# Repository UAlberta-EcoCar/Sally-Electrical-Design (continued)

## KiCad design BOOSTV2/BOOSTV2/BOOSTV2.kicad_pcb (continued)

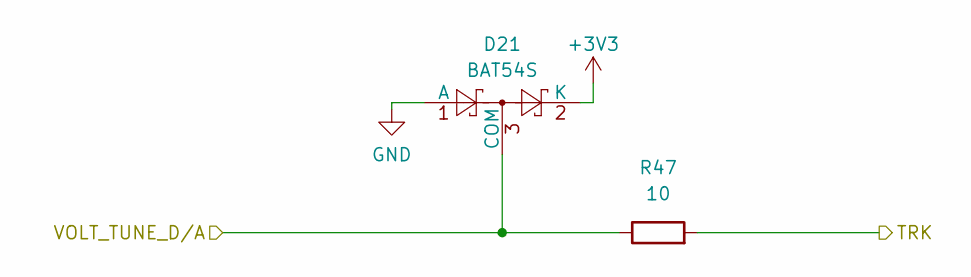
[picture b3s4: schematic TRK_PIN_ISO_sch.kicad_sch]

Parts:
D21: BAT54S; SOT-23
R47: 10; R_0603_1608Metric

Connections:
+3V3: D21.2 (K); also elsewhere on the board
/Boost-Circuit/TRK: R47.2; also elsewhere on the board
/Low Side/VOLT_TUNE_D/A: D21.3 (COM), R47.1; also elsewhere on the board
GND: D21.1 (A); also elsewhere on the board

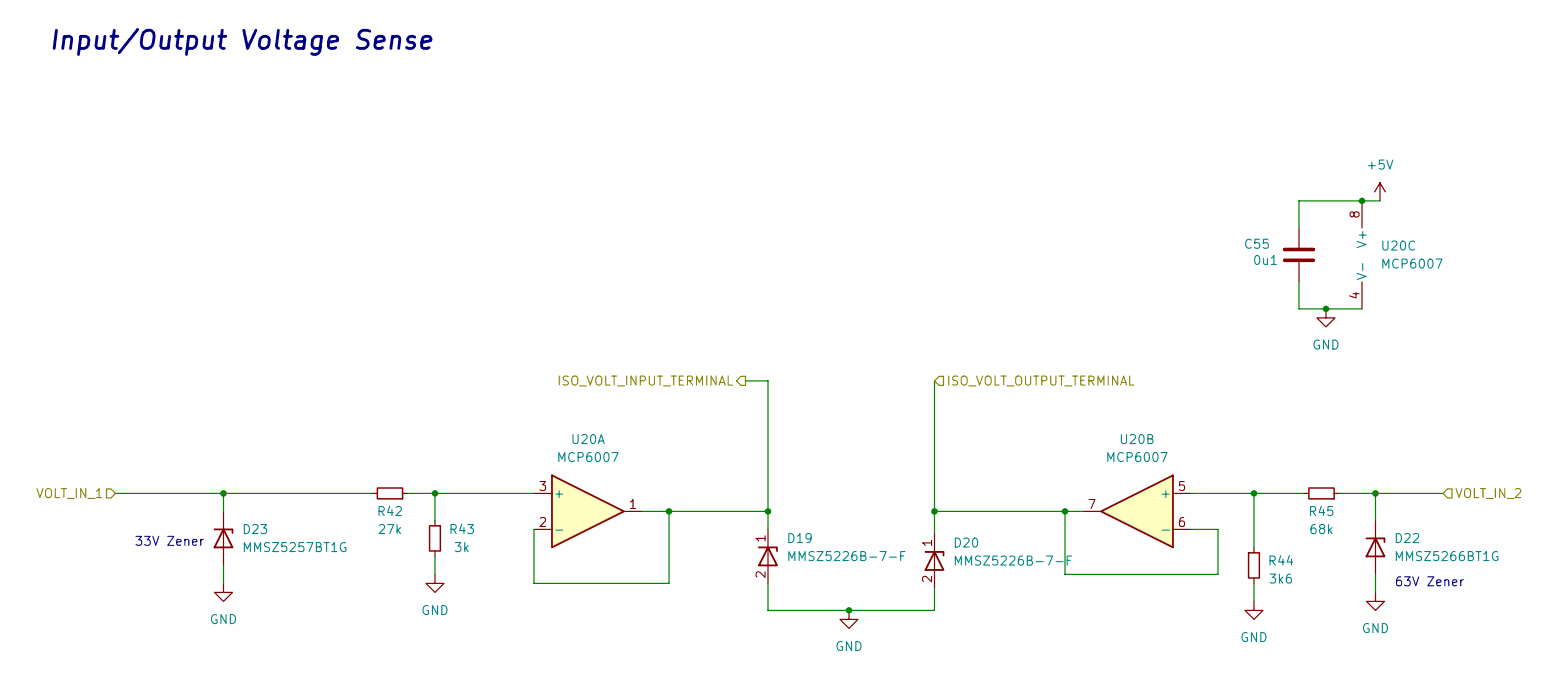
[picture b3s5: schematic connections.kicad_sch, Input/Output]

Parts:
C55: 0u1; C_0603_1608Metric
D19, D20: MMSZ5226B-7-F; D_SOD_123_M; Part# C155250
D22: MMSZ5266BT1G; D_SOD-123
D23: MMSZ5257BT1G; D_SOD-123
R42: 27k; R_0603_1608Metric
R43: 3k; R_0603_1608Metric; Part# C25811
R44: 3k6; R_0603_1608Metric
R45: 68k; R_0603_1608Metric
U20: MCP6007; SOIC-8_3.9x4.9mm_P1.27mm

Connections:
+5V: C55.1, U20.8 (V+); also elsewhere on the board
/Boost-Circuit/VOLT_IN_1: D23.1 (K), R42.2; also elsewhere on the board
/Boost-Circuit/VOLT_IN_2: D22.1 (K), R45.1; also elsewhere on the board
/Low Side/ISO_VOLT_INPUT_TERMINAL: D19.1, U20.1, U20.2 (-); also elsewhere on the board
/Low Side/ISO_VOLT_OUTPUT_TERMINAL: D20.1, U20.6 (-), U20.7; also elsewhere on the board
GND: C55.2, D19.2, D20.2, D22.2 (A), D23.2 (A), R43.2, R44.2, U20.4 (V-); also elsewhere on the board
unnamed: R42.1, R43.1, U20.3 (+)
unnamed: R44.1, R45.2, U20.5 (+)

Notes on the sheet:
33V Zener
Input/Output Voltage Sense
63V Zener

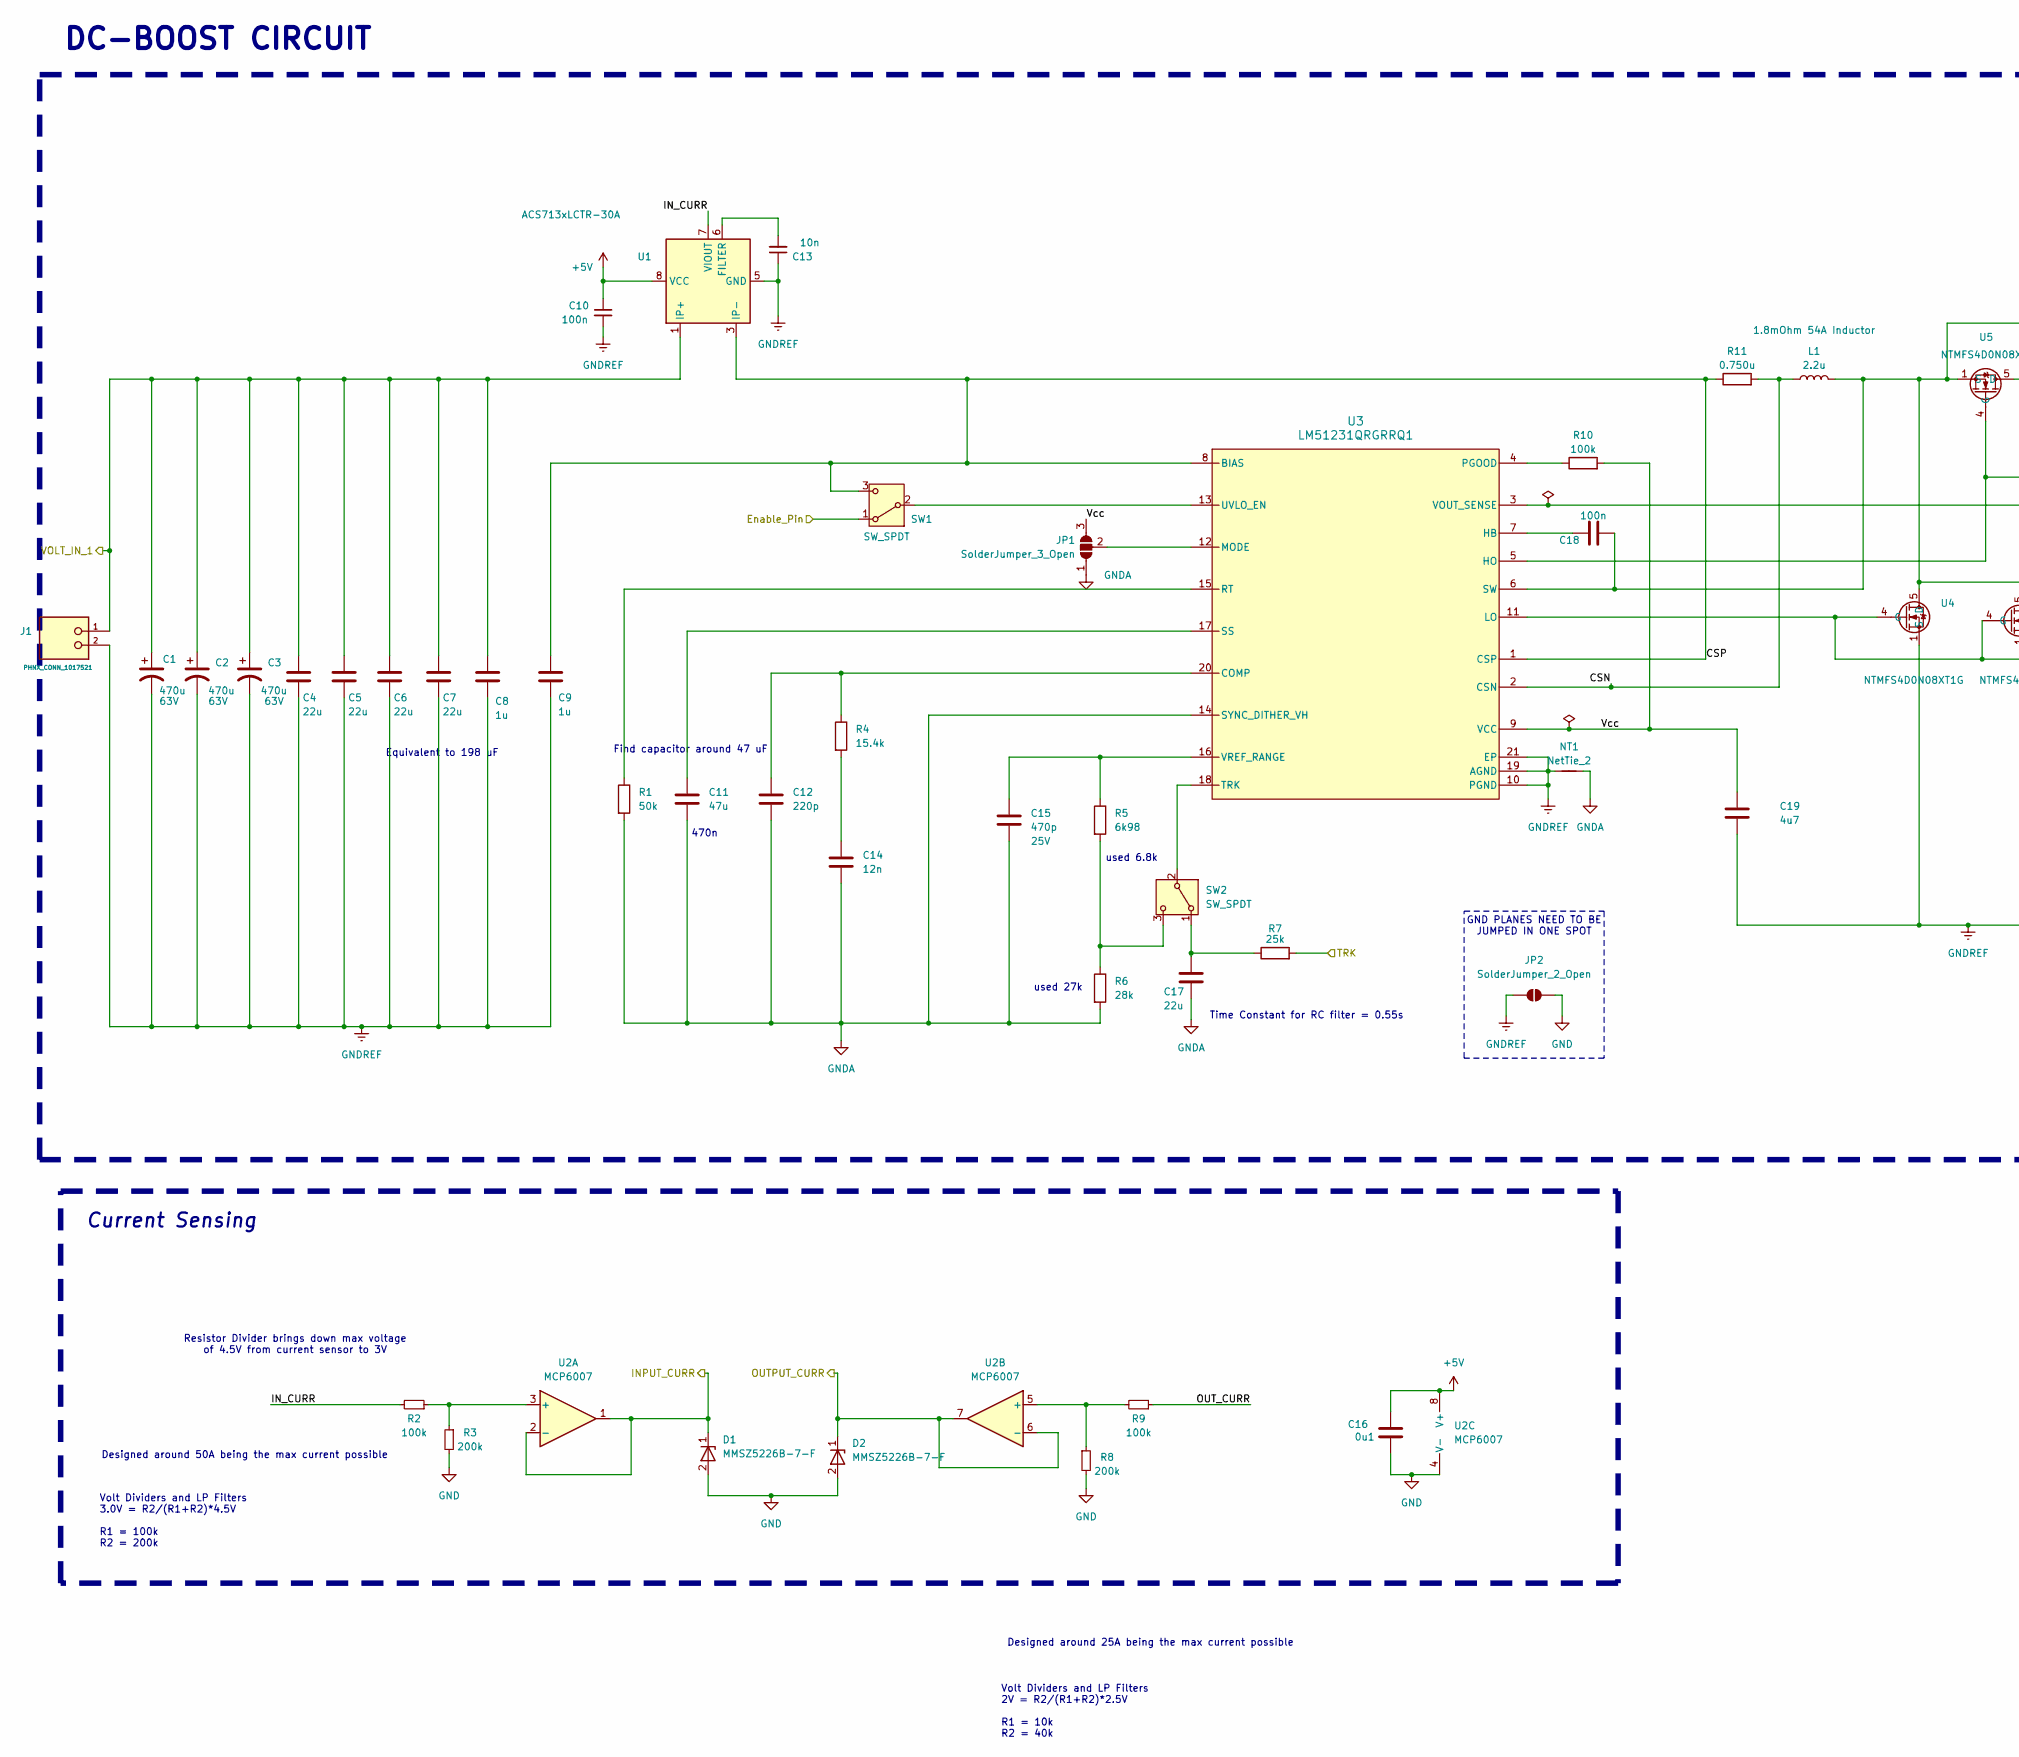
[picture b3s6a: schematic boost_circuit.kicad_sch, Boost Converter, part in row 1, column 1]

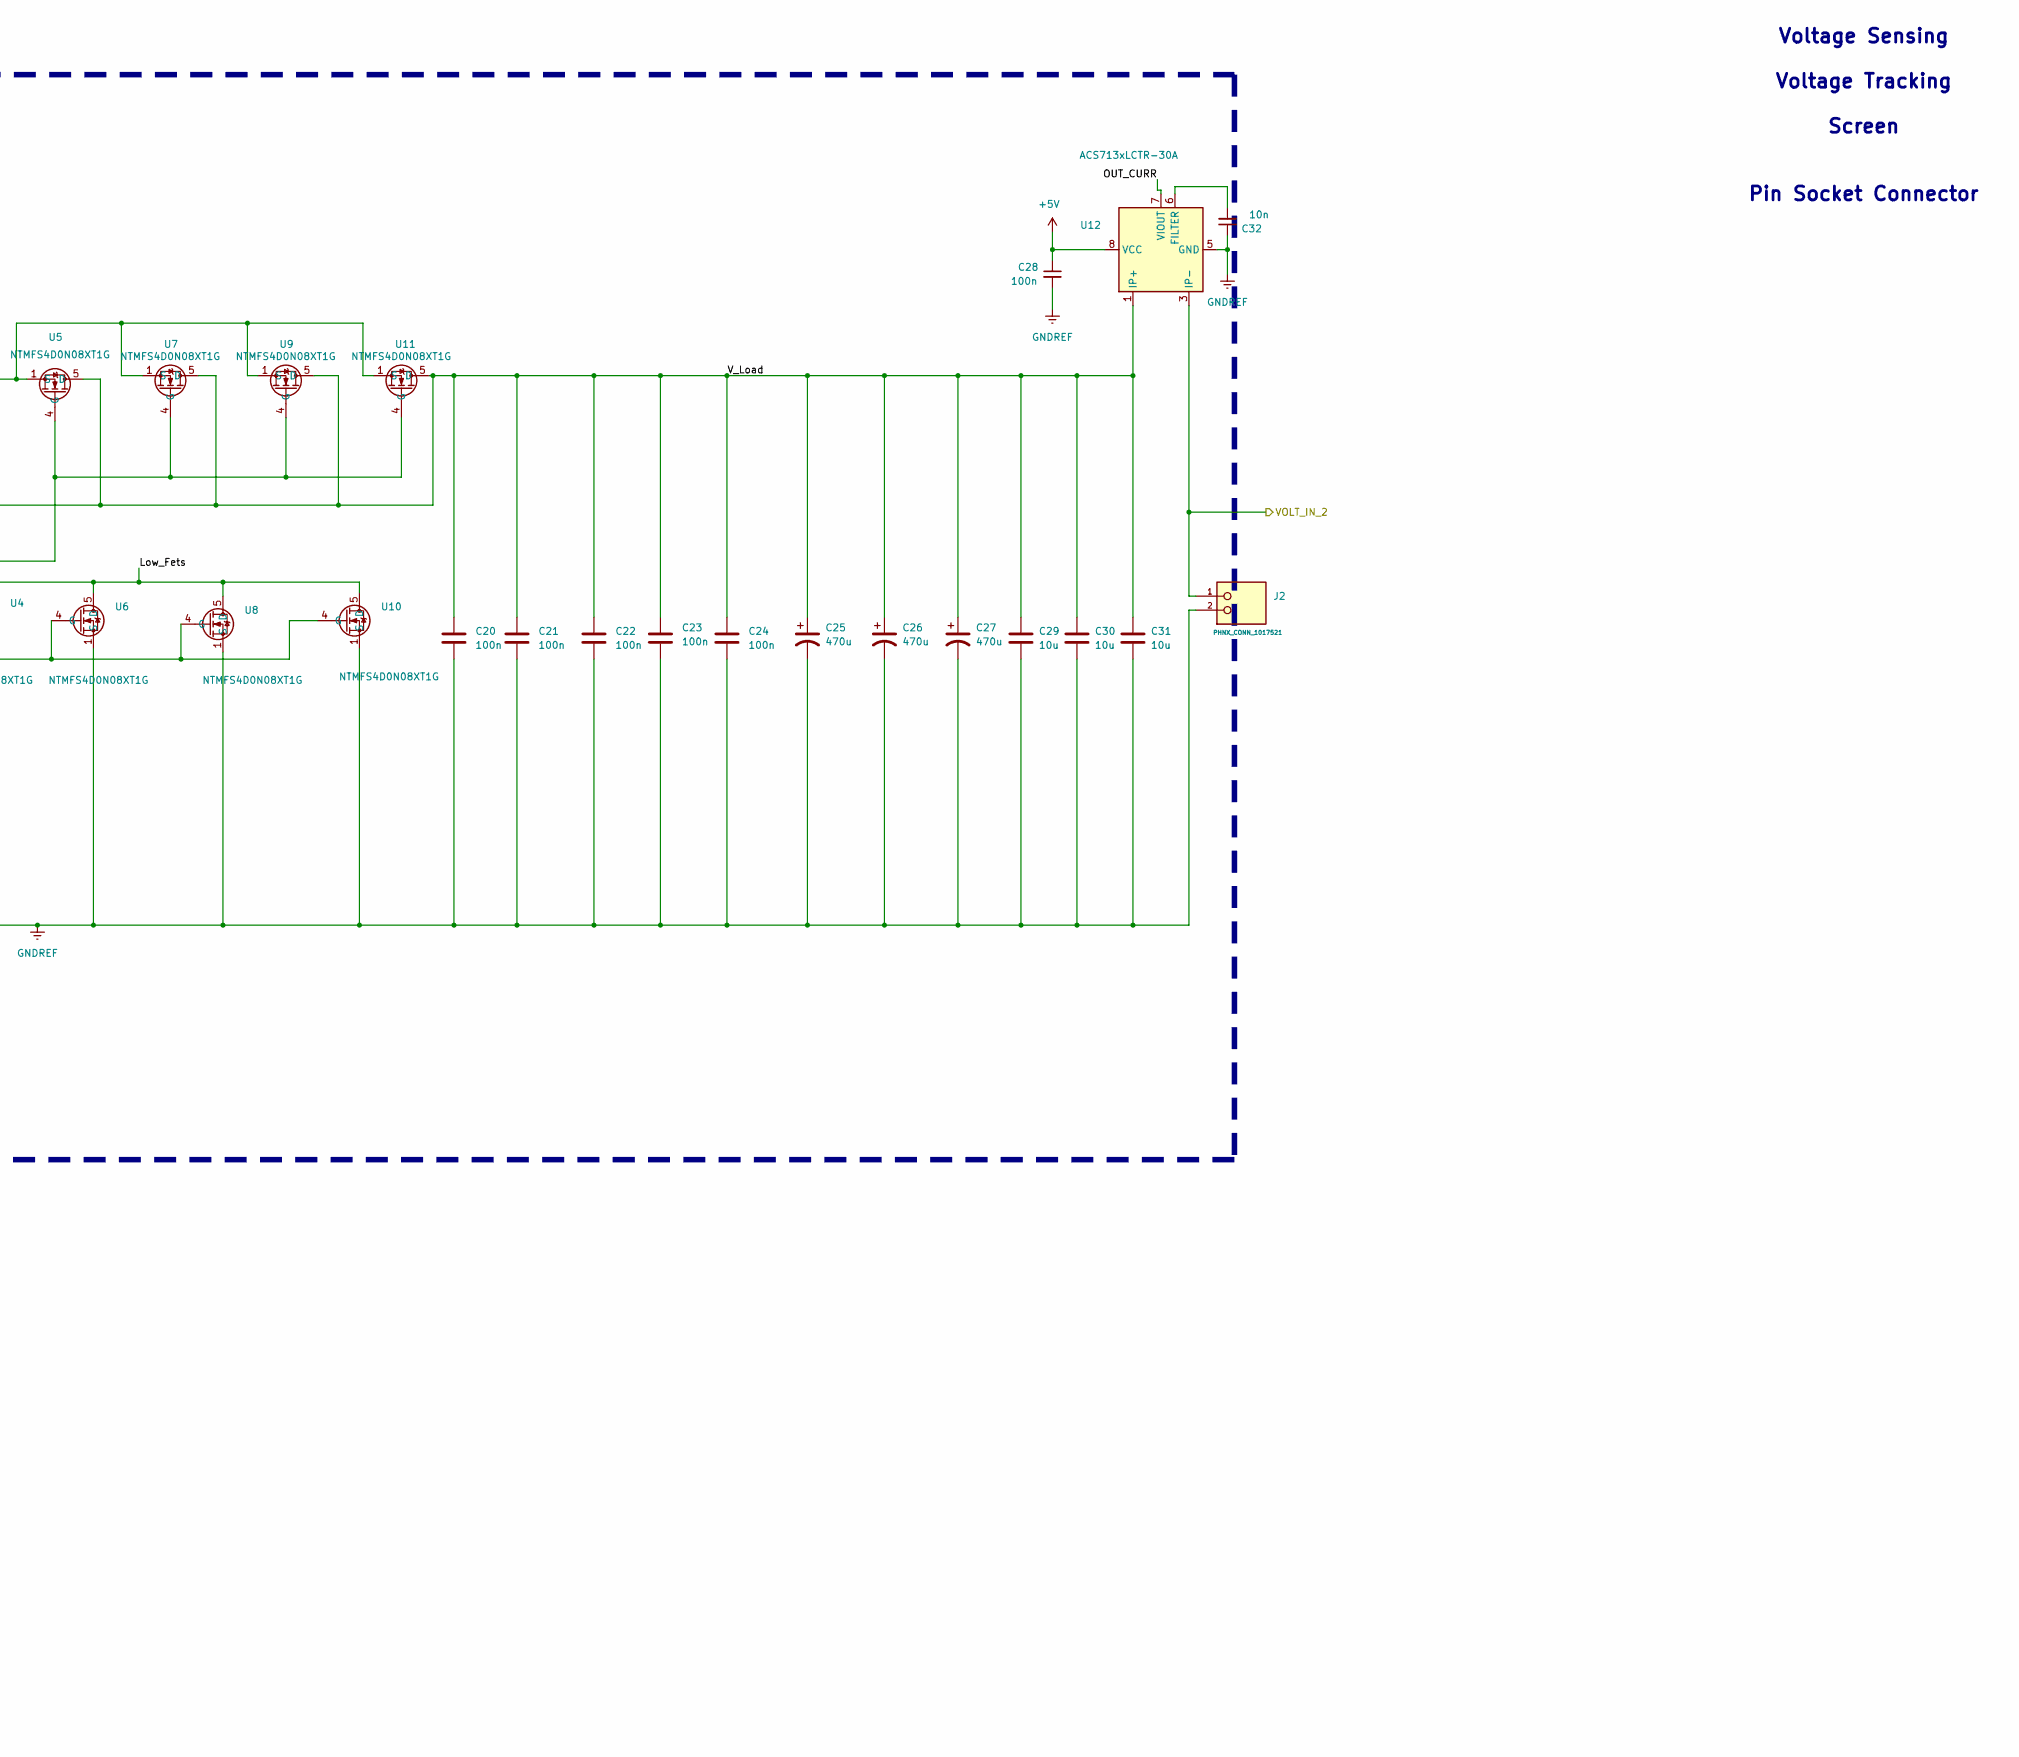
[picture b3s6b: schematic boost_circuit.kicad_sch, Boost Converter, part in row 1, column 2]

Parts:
C1, C2, C3: 470u; CAP_PAN_10X20_PAN; Part # ECA-1HM471B
C4, C5, C6, C7: 22u; C_0805_2012Metric
C8, C9: 1u; C_0603_1608Metric
C10, C28: 100n; C_0603_1608Metric; Part# C88219
C11: 47u; C_0603_1608Metric
C12: 220p; C_0805_2012Metric
C13, C32: 10n; C_0603_1608Metric; Part# C88219
C14: 12n; C_0603_1608Metric
C15: 470p; C_0603_1608Metric; Rating 25V
C16: 0u1; C_0603_1608Metric
C17: 22u; C_0603_1608Metric
C18: 100n; R_0603_1608Metric
C19: 4u7; C_0603_1608Metric
C20, C21, C22, C23, C24: 100n; C_0603_1608Metric
C25, C26, C27: 470u; CAP_YX_16X31P5_RUB; Part # 100ZLH470MEFC16X31.5
C29, C30, C31: 10u; C_1210_3225Metric
D1, D2: MMSZ5226B-7-F; D_SOD_123_M; Part# C155250
J1, J2: PHNX_CONN_1017521; PHOENIX_1017521; PARTREV 04.01.2018
JP1: SolderJumper_3_Open; SolderJumper-3_P1.3mm_Open_RoundedPad1.0x1.5mm_NumberLabels
JP2: SolderJumper_2_Open; SolderJumper-2_P1.3mm_Open_RoundedPad1.0x1.5mm
L1: 2.2u; L_Kemet_3u3
NT1: NetTie_2; NetTie-2_SMD_Pad0.5mm
R1: 50k; R_0603_1608Metric
R2, R9, R10: 100k; R_0603_1608Metric
R3: 200k; R_0603_1608Metric; Part# C25811
R4: 15.4k; R_0603_1608Metric_Pad0.98x0.95mm_HandSolder
R5: 6k98; R_0603_1608Metric
R6: 28k; R_0603_1608Metric
R7: 25k; R_0603_1608Metric
R8: 200k; R_0603_1608Metric
R11: 0.750u; CSS2H3920RL700F
SW1, SW2: SW_SPDT; PinHeader_1x03_P2.54mm_Vertical
U1, U12: ACS713xLCTR-30A; SOIC-8_3.9x4.9mm_P1.27mm
U2: MCP6007; SOIC-8_3.9x4.9mm_P1.27mm
U3: LM51231QRGRRQ1; RGR0020C-MFG
U4, U5, U6, U7, U8, U9, U10, U11: NTMFS4D0N08XT1G; PowerMosDFNHybrid

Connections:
+5V: C10.1, C16.1, C28.1, U1.8 (VCC), U2.8 (V+), U12.8 (VCC); also elsewhere on the board
/Boost-Circuit/CSN: L1.1, R11.2, U3.2 (CSN)
/Boost-Circuit/CSP: C9.1, R11.1, SW1.3 (C), U1.3 (IP-), U1.4 (IP-), U3.1 (CSP), U3.8 (BIAS)
/Boost-Circuit/Enable_Pin: SW1.1 (A); also elsewhere on the board
/Boost-Circuit/INPUT_CURR: D1.1, U2.1, U2.2 (-); also elsewhere on the board
/Boost-Circuit/IN_CURR: R2.2, U1.7 (VIOUT)
/Boost-Circuit/Low_Fets: C18.1, L1.2, U3.6 (SW), U4.5 (D), U5.1 (S), U5.2 (S), U5.3 (S), U6.5 (D), U7.1 (S), U7.2 (S), U7.3 (S), U8.5 (D), U9.1 (S), U9.2 (S), U9.3 (S), U10.5 (D), U11.1 (S), U11.2 (S), U11.3 (S)
/Boost-Circuit/OUTPUT_CURR: D2.1, U2.6 (-), U2.7; also elsewhere on the board
/Boost-Circuit/OUT_CURR: R9.1, U12.7 (VIOUT)
/Boost-Circuit/TRK: R7.2; also elsewhere on the board
/Boost-Circuit/VOLT_IN_1: C1.1, C2.1, C3.1, C4.1, C5.1, C6.1, C7.1, C8.1, J1.1, U1.1 (IP+), U1.2 (IP+); also elsewhere on the board
/Boost-Circuit/VOLT_IN_2: J2.1, U12.3 (IP-), U12.4 (IP-); also elsewhere on the board
/Boost-Circuit/V_Load: C20.1, C21.1, C22.1, C23.1, C24.1, C25.1, C26.1, C27.1, C29.1, C30.1, C31.1, U3.3 (VOUT_SENSE), U5.5 (D), U7.5 (D), U9.5 (D), U11.5 (D), U12.1 (IP+), U12.2 (IP+)
/Boost-Circuit/Vcc: C19.1, JP1.3 (B), R10.2, U3.9 (VCC)
GND: C16.2, D1.2, D2.2, JP2.2 (B), R3.2, R8.2, U2.4 (V-); also elsewhere on the board
GNDA: C11.2, C12.2, C14.2, C15.2, C17.2, JP1.1 (A), NT1.2, R1.2, R6.2, U3.14 (SYNC_DITHER_VH)
GNDREF: C1.2, C2.2, C3.2, C4.2, C5.2, C6.2, C7.2, C8.2, C9.2, C10.2, C13.1, C19.2, C20.2, C21.2, C22.2, C23.2, C24.2, C25.2, C26.2, C27.2, C28.2, C29.2, C30.2, C31.2, C32.1, J1.2, J2.2, JP2.1 (A), NT1.1, U1.5 (GND), U3.10 (PGND), U3.19 (AGND), U3.21 (EP), U4.1 (S), U4.2 (S), U4.3 (S), U6.1 (S), U6.2 (S), U6.3 (S), U8.1 (S), U8.2 (S), U8.3 (S), U10.1 (S), U10.2 (S), U10.3 (S), U12.5 (GND)
unnamed: C14.1, R4.2
unnamed: JP1.2 (C), U3.12 (MODE)
unnamed: SW1.2 (B), U3.13 (UVLO_EN)
unnamed: C17.1, R7.1, SW2.1 (A)
unnamed: SW2.2 (B), U3.18 (TRK)
unnamed: R5.2, R6.1, SW2.3 (C)
unnamed: C13.2, U1.6 (FILTER)
unnamed: R2.1, R3.1, U2.3 (+)
unnamed: R8.1, R9.2, U2.5 (+)
unnamed: C12.1, R4.1, U3.20 (COMP)
unnamed: C18.2, U3.7 (HB)
unnamed: R10.1, U3.4 (PGOOD)
unnamed: R1.1, U3.15 (RT)
unnamed: C11.1, U3.17 (SS)
unnamed: C15.1, R5.1, U3.16 (VREF_RANGE)
unnamed: U3.11 (LO), U4.4 (G), U6.4 (G), U8.4 (G), U10.4 (G)
unnamed: U3.5 (HO), U5.4 (G), U7.4 (G), U9.4 (G), U11.4 (G)
unnamed: C32.2, U12.6 (FILTER)

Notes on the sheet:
used 27k
DC-BOOST CIRCUIT
Resistor Divider brings down max voltage of 4.5V from current sensor to 3V
470n
used 6.8k
Volt Dividers and LP Filters 3.0V = R2/(R1+R2)*4.5V R1 = 100k R2 = 200k
Time Constant for RC filter = 0.55s
Volt Dividers and LP Filters 2V = R2/(R1+R2)*2.5V R1 = 10k R2 = 40k
Current Sensing
GND PLANES NEED TO BE JUMPED IN ONE SPOT
Voltage Sensing Voltage Tracking Screen Pin Socket Connector
Designed around 25A being the max current possible
Find capacitor around 47 uF
Designed around 50A being the max current possible
Equivalent to 198 uF

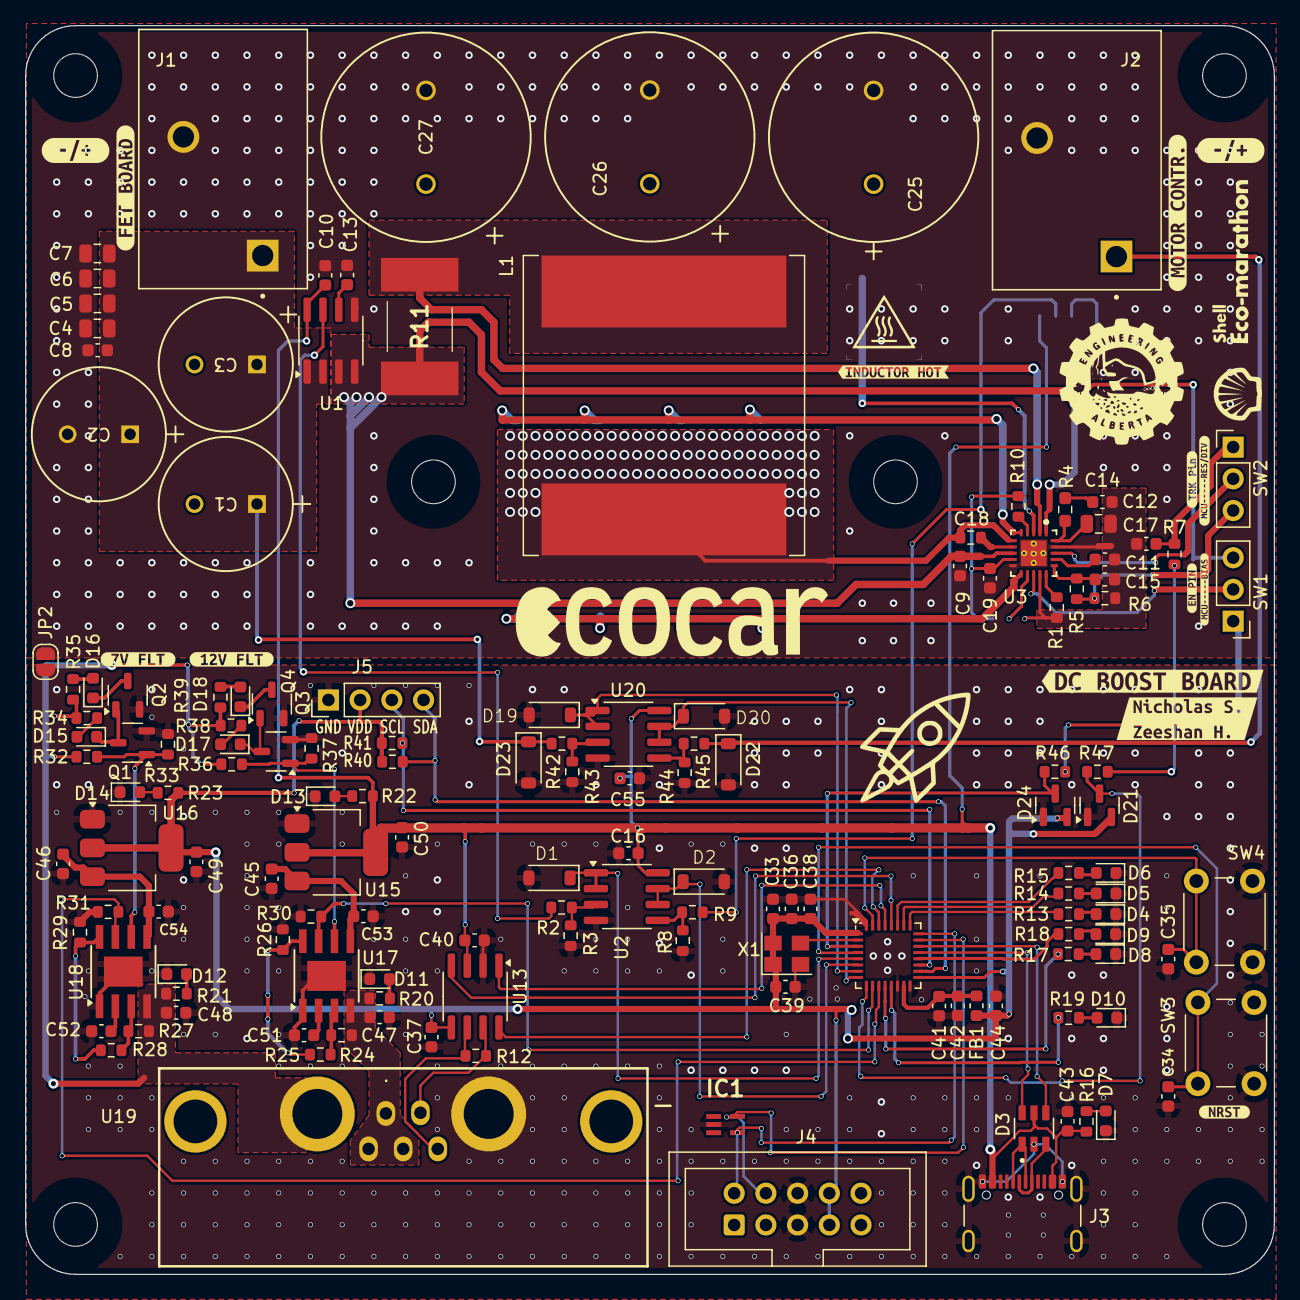
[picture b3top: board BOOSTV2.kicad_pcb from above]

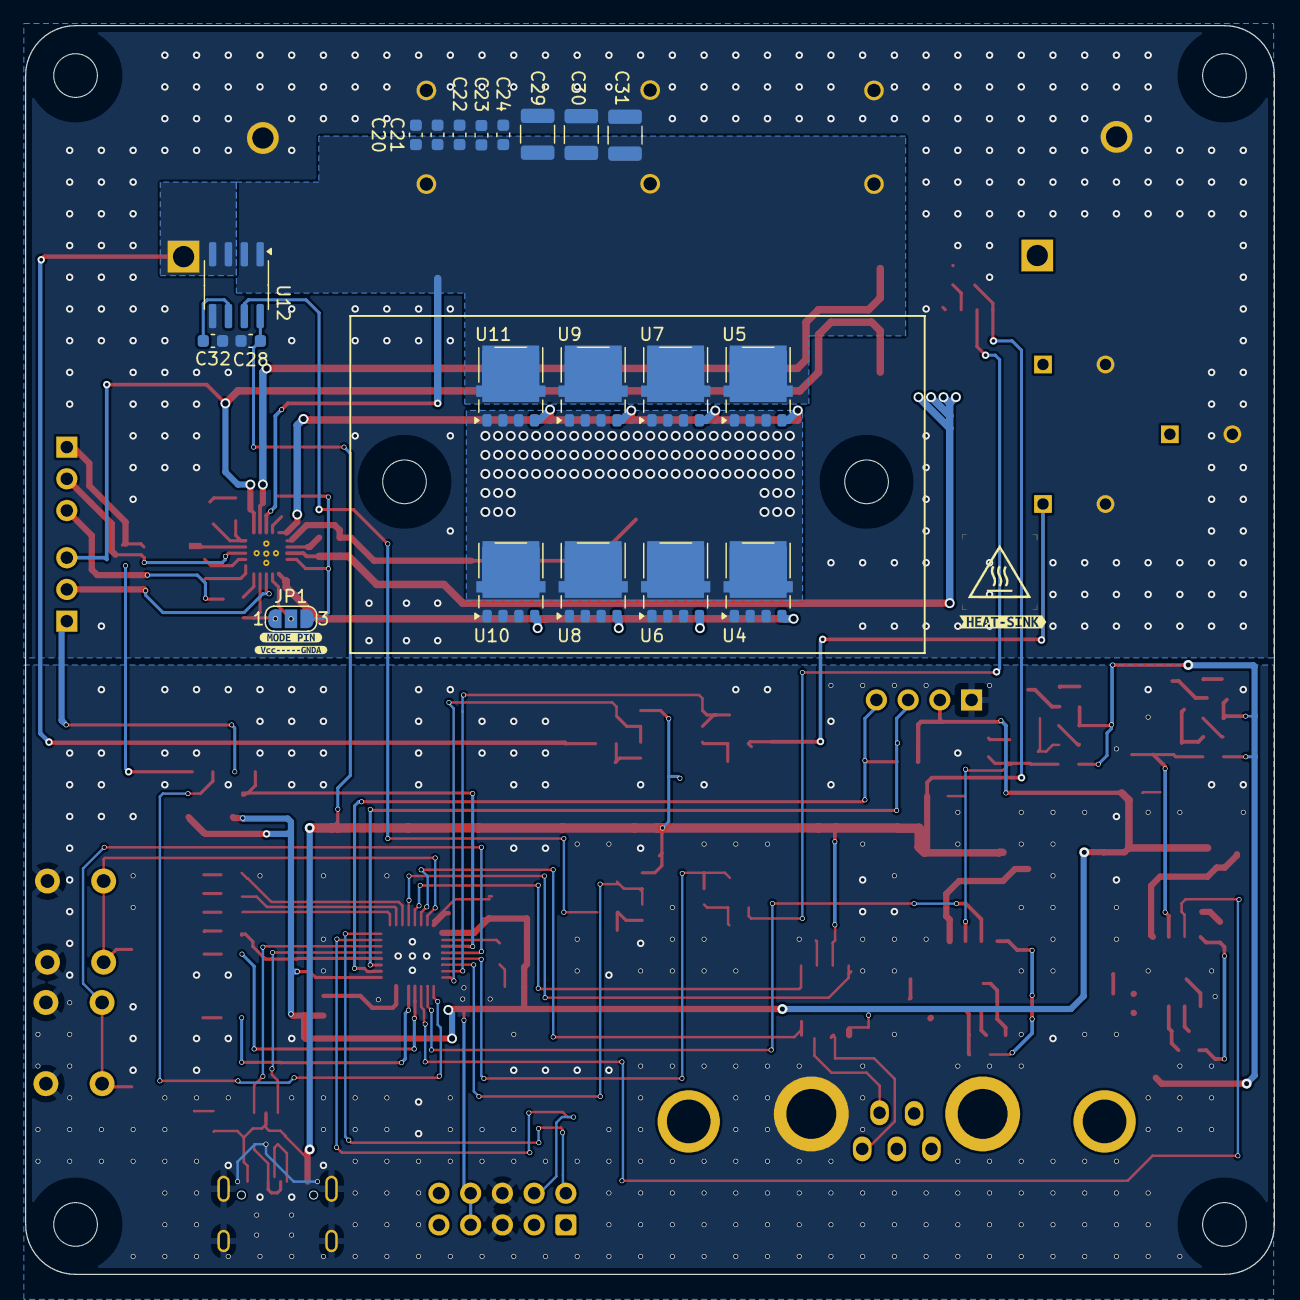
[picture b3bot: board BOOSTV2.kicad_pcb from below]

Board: 2 copper layers, 100.0 x 100.0 mm, 189 parts (23 on the bottom side), 98 nets.

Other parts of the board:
kibuzzard-67B8F6AB: G***; kibuzzard-67B8F6AB
kibuzzard-67B8F68E: G***; kibuzzard-67B8F68E
kibuzzard-67B8F697: G***; kibuzzard-67B8F697
kibuzzard-67B37C45: G***; kibuzzard-67B37C45
kibuzzard-67B37DE2: G***; kibuzzard-67B37DE2
kibuzzard-67B58E6E: G***; kibuzzard-67B58E6E
kibuzzard-67B58E58: G***; kibuzzard-67B58E58
kibuzzard-67B540FD: G***; kibuzzard-67B540FD
kibuzzard-67B591A9: G***; kibuzzard-67B591A9
kibuzzard-67B59132: G***; kibuzzard-67B59132
kibuzzard-67BA3C10: G***; kibuzzard-67BA3C10
kibuzzard-67BA360B: G***; kibuzzard-67BA360B
kibuzzard-67BA362A: G***; kibuzzard-67BA362A
kibuzzard-6743FE6D: G***; kibuzzard-6743FE6D
kibuzzard-6743FE8B: G***; kibuzzard-6743FE8B
kibuzzard-67392652, kibuzzard-67392652#2: G***; kibuzzard-67392652

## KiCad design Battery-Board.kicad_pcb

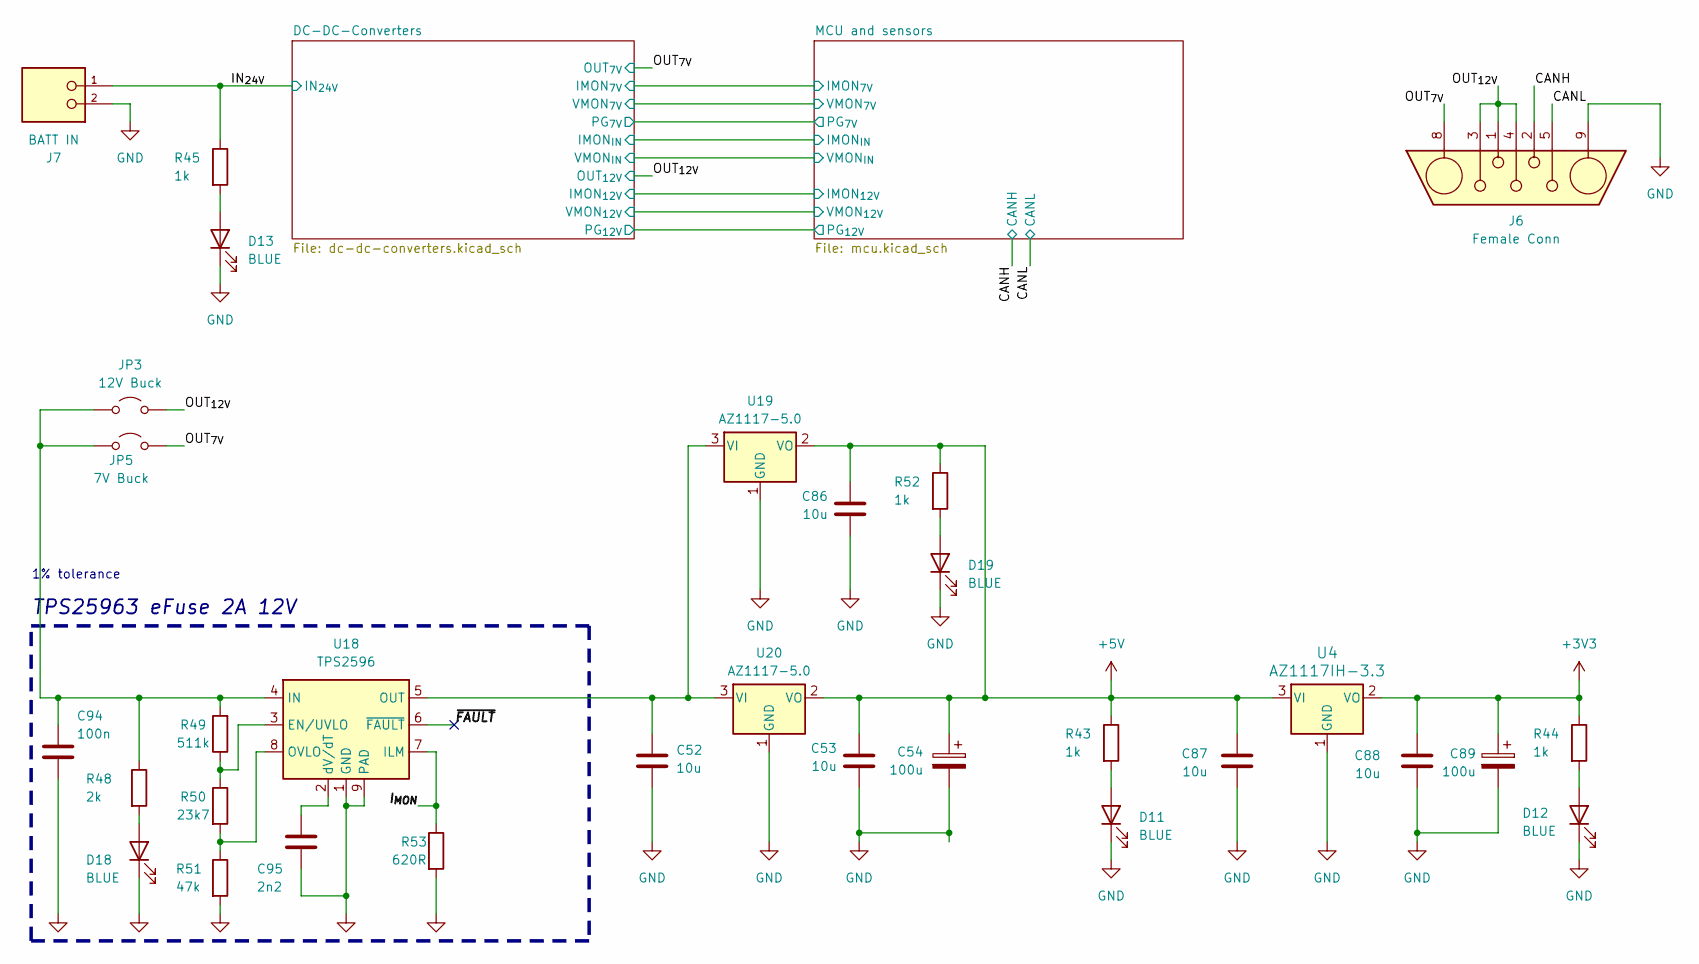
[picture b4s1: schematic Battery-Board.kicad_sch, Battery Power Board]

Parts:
C52, C53, C86, C87, C88: 10u; C_0805_2012Metric; LCSC# C15850
C54, C89: 100u; CP_Elec_6.3x9.9; LCSC# C72478
C94: 100n; C_0603_1608Metric; JLCPCB Part#(Optional) C28233
C95: 2n2; C_0603_1608Metric; JLCPCB Part#(Optional) C1531
D11, D12, D13, D18, D19: BLUE; LED_0603_1608Metric
J6: Female Conn; DB7W2-Female
J7: BATT IN; PHOENIX_1017521; PARTREV 04.01.2018
JP3: 12V Buck; J_0603_Triangular
JP5: 7V Buck; J_0603_Triangular
R43, R44, R45, R52: 1k; R_0603_1608Metric
R48: 2k; R_0603_1608Metric; JLCPCB Part#(Optional) C17604
R49: 511k; R_0603_1608Metric; JLCPCB Part#(optional) C17709
R50: 23k7; R_0603_1608Metric; JLCPCB Part#(optional) C17480
R51: 47k; R_0603_1608Metric; JLCPCB Part#(optional) C17713
R53: 620R; R_0603_1608Metric; JLCPCB Part#(Optional) C23220
U4: AZ1117IH-3.3; SOT-223-3_TabPin2
U18: TPS2596; TI_SO-PowerPAD-8
U19, U20: AZ1117-5.0; SOT-223-3_TabPin2

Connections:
+3V3: C88.1, C89.1, R44.1, U4.2 (VO); also elsewhere on the board
+5V: C53.1, C54.1, C86.1, C87.1, R43.1, R52.1, U4.3 (VI), U19.2 (VO), U20.2 (VO); also elsewhere on the board
/CANH: J6.2; also elsewhere on the board
/CANL: J6.5; also elsewhere on the board
/IN_{24V}: J7.1, R45.1; also elsewhere on the board
/I_{MON}: R53.1, U18.7 (ILM)
/OUT_{7V}: J6.8, JP5.2 (B); also elsewhere on the board
/OUT_{12V}: J6.1, J6.3, J6.4, JP3.2 (B); also elsewhere on the board
/~FAULT: U18.6 (~FAULT)
GND: C52.2, C53.2, C54.2, C86.2, C87.2, C88.2, C89.2, C94.2, C95.2, D11.1 (K), D12.1 (K), D13.1 (K), D18.1 (K), D19.1 (K), J6.9, J7.2, R51.2, R53.2, U4.1 (GND), U18.1 (GND), U18.9 (PAD), U19.1 (GND), U20.1 (GND); also elsewhere on the board
unnamed: D11.2 (A), R43.2
unnamed: D12.2 (A), R44.2
unnamed: D13.2 (A), R45.2
unnamed: D18.2 (A), R48.2
unnamed: D19.2 (A), R52.2
unnamed: C94.1, JP3.1 (A), JP5.1 (A), R48.1, R49.2, U18.4 (IN)
unnamed: R49.1, R50.1, U18.3 (EN/UVLO)
unnamed: C52.1, U18.5 (OUT), U19.3 (VI), U20.3 (VI)
unnamed: R50.2, R51.1, U18.8 (OVLO)
unnamed: C95.1, U18.2 (dV/dT)

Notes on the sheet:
TPS25963 eFuse 2A 12V
1% tolerance

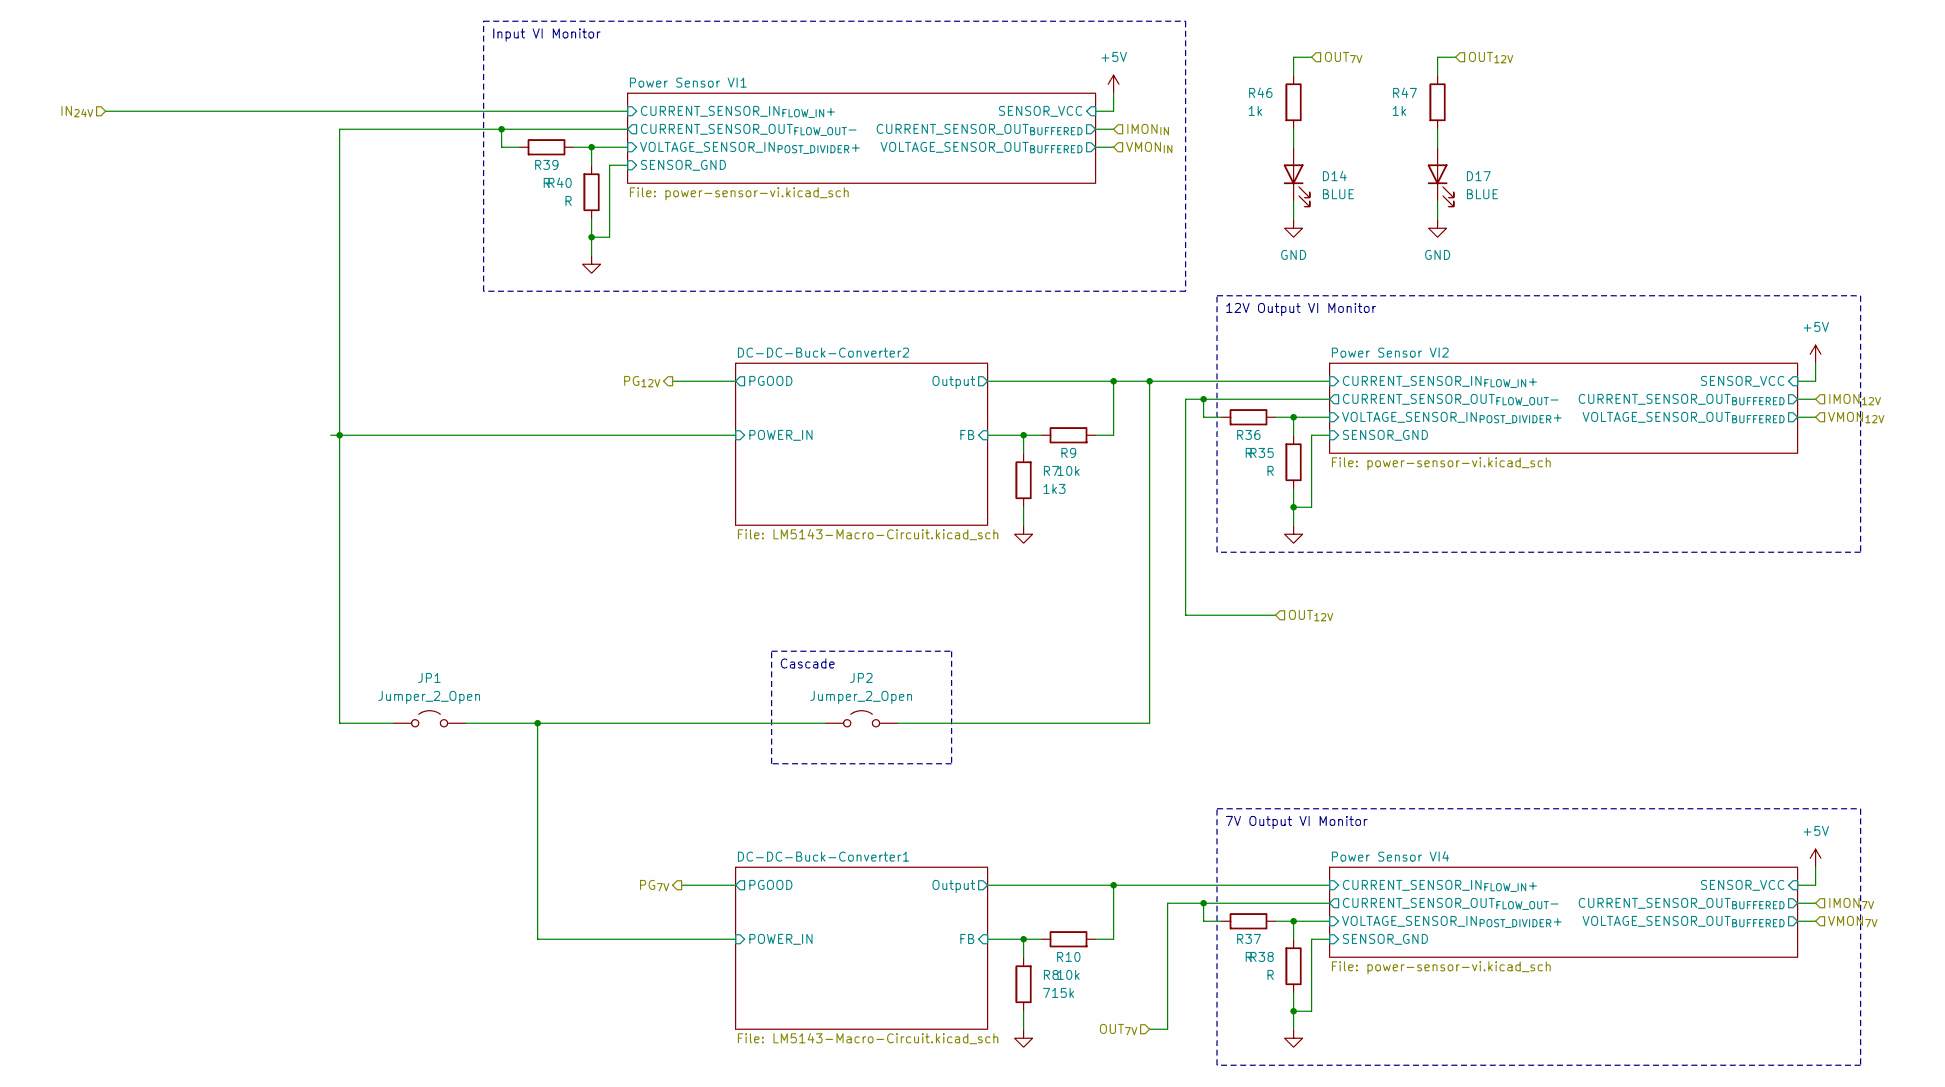
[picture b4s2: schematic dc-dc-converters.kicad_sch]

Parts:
D14, D17: BLUE; LED_0603_1608Metric
JP1, JP2: Jumper_2_Open; Jumper_Micro-Miniature_P5.375mm
R7: 1k3; R_0603_1608Metric
R8: 715k; R_0603_1608Metric
R9, R10: 10k; R_0603_1608Metric
R35, R36, R37, R38, R39, R40: R; R_0603_1608Metric
R46, R47: 1k; R_0603_1608Metric

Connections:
/DC-DC-Converters/DC-DC-Buck-Converter1/FB: R8.2, R10.1; also elsewhere on the board
/DC-DC-Converters/DC-DC-Buck-Converter1/Output: R10.2; also elsewhere on the board
/DC-DC-Converters/DC-DC-Buck-Converter1/POWER_IN: JP1.2 (B), JP2.1 (A); also elsewhere on the board
/DC-DC-Converters/DC-DC-Buck-Converter2/FB: R7.2, R9.1; also elsewhere on the board
/DC-DC-Converters/DC-DC-Buck-Converter2/Output: JP2.2 (B), R9.2; also elsewhere on the board
/DC-DC-Converters/DC-DC-Buck-Converter2/POWER_IN: JP1.1 (A), R39.2; also elsewhere on the board
/DC-DC-Converters/Power Sensor VI1/VOLTAGE_SENSOR_IN_{POST_DIVIDER}+: R39.1, R40.2; also elsewhere on the board
/DC-DC-Converters/Power Sensor VI2/VOLTAGE_SENSOR_IN_{POST_DIVIDER}+: R35.2, R36.1; also elsewhere on the board
/DC-DC-Converters/Power Sensor VI4/VOLTAGE_SENSOR_IN_{POST_DIVIDER}+: R37.1, R38.2; also elsewhere on the board
/OUT_{7V}: R37.2, R46.1; also elsewhere on the board
/OUT_{12V}: R36.2, R47.1; also elsewhere on the board
GND: D14.1 (K), D17.1 (K), R7.1, R8.1, R35.1, R38.1, R40.1; also elsewhere on the board
unnamed: D14.2 (A), R46.2
unnamed: D17.2 (A), R47.2

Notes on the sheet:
12V Output VI Monitor
7V Output VI Monitor
Input VI Monitor
Cascade
